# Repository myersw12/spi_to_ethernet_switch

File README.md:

# spi_to_ethernet_switch
Hardware and software for an Ethernet Switch with an MII to SPI adapter on it.

## Description

This project has 2 parts; a Kicad Project containing the schematic and layout for the board, and the software to interact 
with the board.  The idea was to create a compact ethernet switch suitable for use with low power microcontrollers and single 
board computers.  Micrel produces several ethernet switches in the same family with more ports and this design would make a good 
starting point for using those.

## Kicad Project

The main components of this project are the [Micrel KSZ8863MLL](https://www.microchip.com/wwwproducts/en/KSZ8863) 3 Port Ethernet Switch and the Wiznet W3150A+ Ethernet MAC to SPI Adapter.
The KSZ8863MLL provides 3 ethernet interfaces.  The first 2 include the PHYs and are connected to RJ45 connectors with included magnetics.
The other interface is connected via the MII interface to the [W3150A+](http://www.wiznet.io/product-item/w3150a/).  The SPI pins on W3150A+ are broken out on the board so that they
may be attached to a microcontroller or single board computer.  All of the examples in this project use a Raspberry Pi 2.

## Software

The software is located in the [code](/code) directory.  This was written for the Raspberry Pi 2 and it is easiest to compile it
on the raspberry pi.  Once it is there, run the makefile in the [src](/code/src) directory.  This creates three executables:
  * tx_example: transmits a raw ethernet frame once a second
  * recv_example: receives raw ethernet frames and prints them as they arrive
  * tap_example: uses the tap interface on the Raspberry Pi to send and receive raw ethernet frames over the SPI interface
  
The W3150A+ offers TCP/IP processing onboard.  Depending on the situation, it might be advantageous to make use of that functionality.
The existing SPI connection will support this.

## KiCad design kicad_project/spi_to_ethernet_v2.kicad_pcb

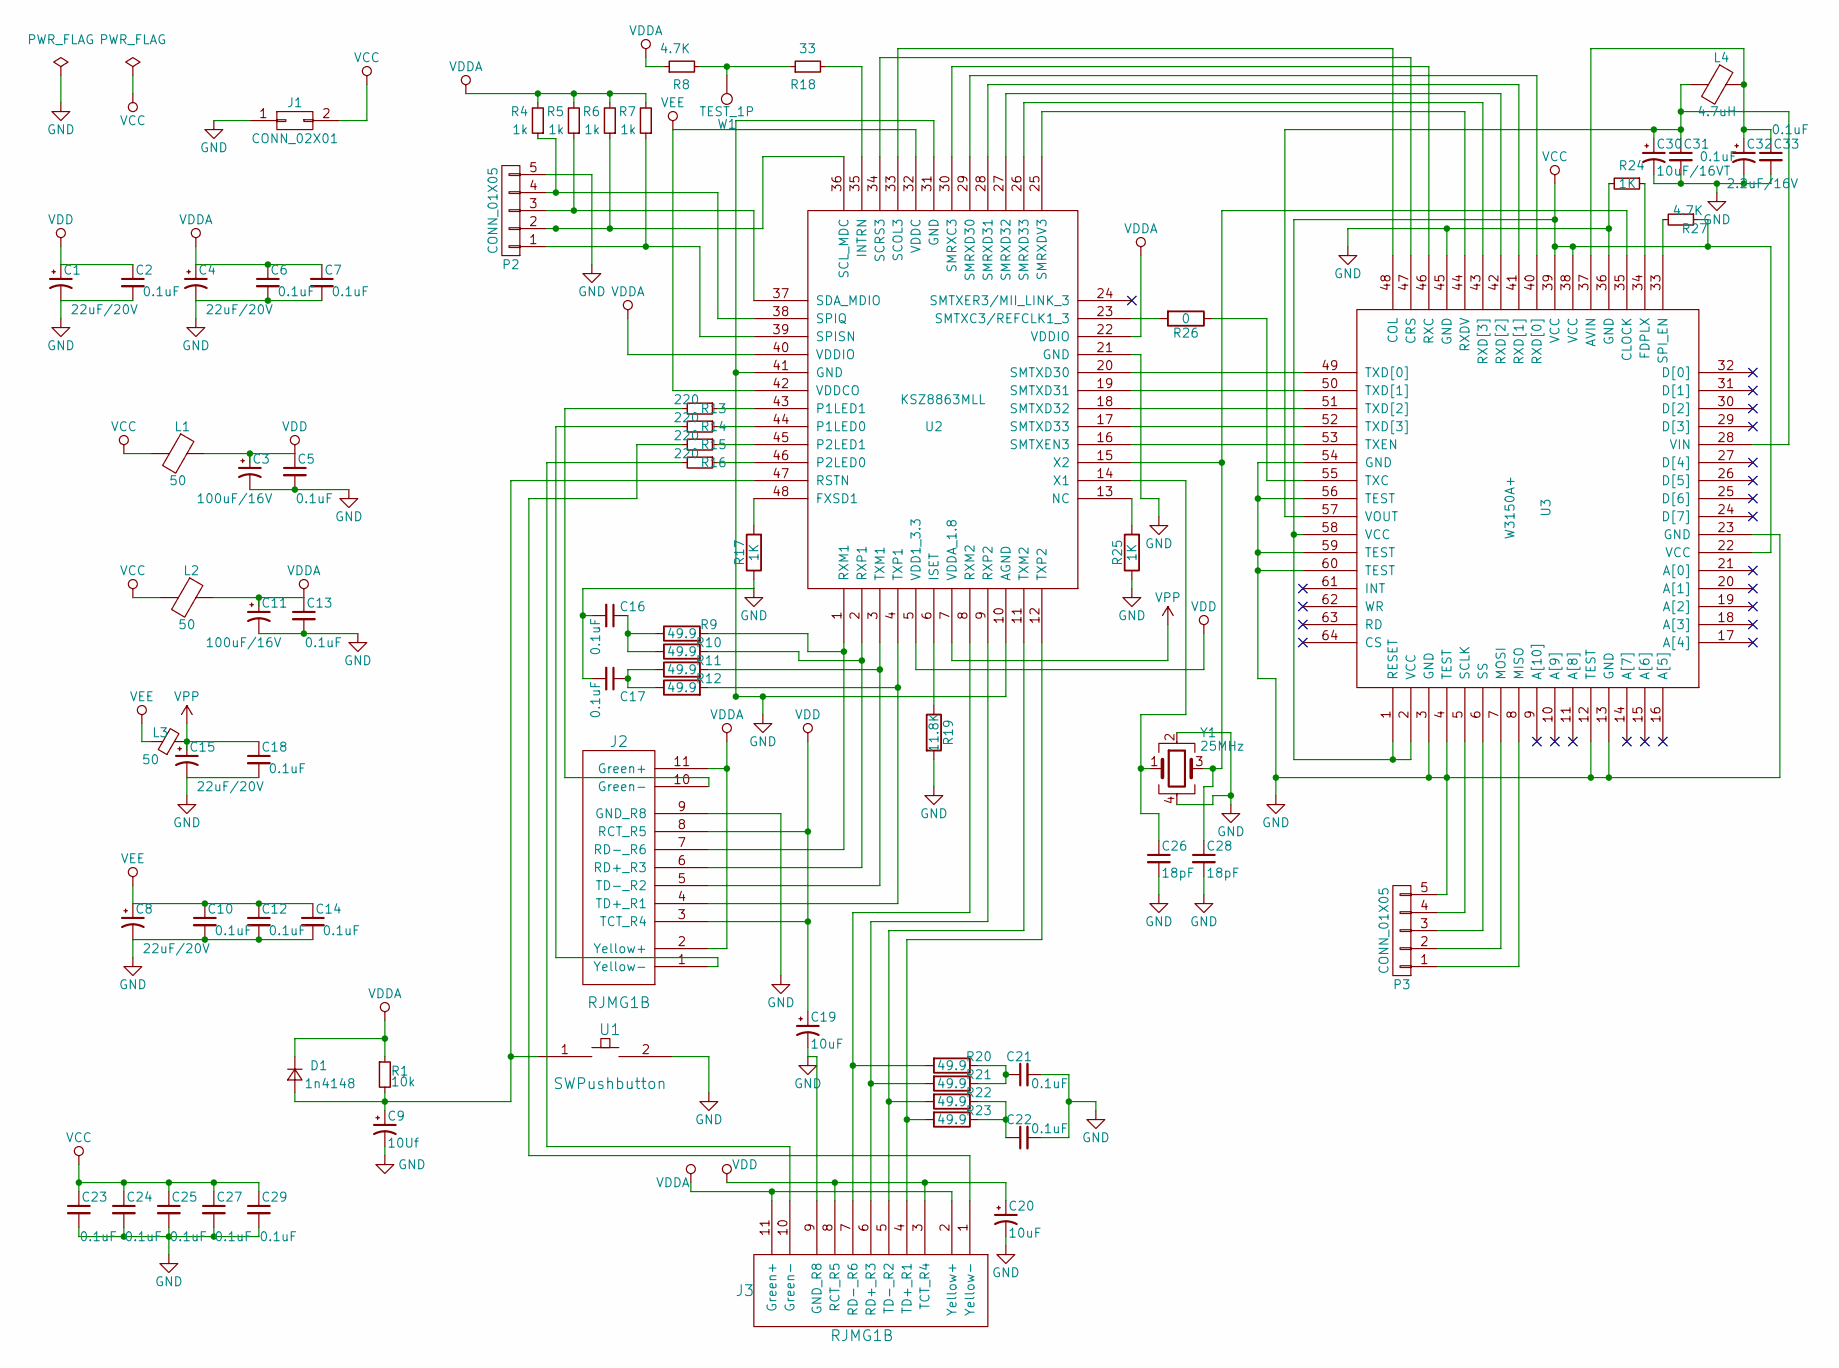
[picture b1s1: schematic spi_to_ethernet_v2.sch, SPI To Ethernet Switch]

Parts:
C1, C4, C8, C15: 22uF/20V; C_0805_HandSoldering
C2, C5, C6, C7, C10, C12, C13, C14, C16, C17, C18, C21, C22, C23, C24, C25, C27, C29, C31, C33: 0.1uF; C_0402
C3, C11: 100uF/16V; C_1210_HandSoldering
C9: 10Uf; C_0603_HandSoldering
C19, C20: 10uF; C_0603_HandSoldering
C26, C28: 18pF; C_0402
C30: 10uF/16VT; C_0603_HandSoldering
C32: 2.2uF/16V; C_0603_HandSoldering
D1: 1n4148; D_SOD-123
J1: CONN_02X01; Pin_Header_Straight_2x01_Pitch2.54mm
J2, J3: RJMG1B
L1, L2, L3: 50; C_1206_HandSoldering
L4: 4.7uH; C_1206_HandSoldering
P2, P3: CONN_01X05; Pin_Header_Straight_1x05_Pitch2.54mm
R1: 10k; R_0402
R4, R5, R6, R7: 1k; R_0402
R8, R27: 4.7K; R_0402
R9, R10, R11, R12, R20, R21, R22, R23: 49.9; R_0402
R13, R14, R15, R16: 220; R_0402
R17, R24, R25: 1K; R_0402
R18: 33; R_0402
R19: 11.8K; R_0402
R26: 0; R_0402
U1: SWPushbutton; SW_SPST_EVQQ2
U2: KSZ8863MLL; LQFP-48_7x7mm_Pitch0.5mm
U3: W3150A+; LQFP-64_10x10mm_Pitch0.5mm
W1: TEST_1P; Measurement_Point_Round-SMD-Pad_Big
Y1: 25MHz; Crystal_SMD_Abracon_ABM8G-4pin_3.2x2.5mm

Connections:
GND: C1.2, C2.2, C3.2, C4.2, C5.2, C6.2, C7.2, C8.2, C9.2, C10.2, C11.2, C12.2, C13.2, C14.2, C15.2, C16.2, C17.2, C18.2, C19.2, C20.2, C21.2, C22.2, C23.2, C24.2, C25.2, C26.2, C27.2, C28.2, C29.2, C30.2, C31.2, C32.2, C33.2, J1.1, J2.9 (GND_R8), J3.9 (GND_R8), P2.5, P3.5, R17.1, R19.2, R24.2, R25.1, U1.2, U2.10 (AGND), U2.21 (GND), U2.31 (GND), U2.41 (GND), U3.3 (GND), U3.4 (TEST), U3.12 (TEST), U3.13 (GND), U3.23 (GND), U3.36 (GND), U3.45 (GND), U3.54 (GND), U3.56 (TEST), U3.59 (TEST), U3.60 (TEST), Y1.2, Y1.4
unnamed: C9.1, D1.2 (A), R1.2, U1.1, U2.47 (RSTN)
unnamed: C16.1, R9.1, R10.1
unnamed: C17.1, R11.1, R12.1
unnamed: C21.1, R20.1, R21.1
unnamed: C22.1, R22.1, R23.1
unnamed: C26.1, U2.14 (X1), Y1.1
unnamed: C28.1, U2.15 (X2), U3.35 (CLOCK), Y1.3
unnamed: C30.1, C31.1, L4.2, U3.28 (VIN), U3.57 (VOUT)
unnamed: C32.1, C33.1, L4.1, U3.37 (AVIN)
unnamed: J2.1 (Yellow-), R14.2
unnamed: J2.4 (TD+_R1), R12.2, U2.4 (TXP1)
unnamed: J2.5 (TD-_R2), R11.2, U2.3 (TXM1)
unnamed: J2.6 (RD+_R3), R10.2, U2.2 (RXP1)
unnamed: J2.7 (RD-_R6), R9.2, U2.1 (RXM1)
unnamed: J2.10 (Green-), R13.2
unnamed: J3.1 (Yellow-), R15.2
unnamed: J3.4 (TD+_R1), R23.2, U2.12 (TXP2)
unnamed: J3.5 (TD-_R2), R22.2, U2.11 (TXM2)
unnamed: J3.6 (RD+_R3), R21.2, U2.9 (RXP2)
unnamed: J3.7 (RD-_R6), R20.2, U2.8 (RXM2)
unnamed: J3.10 (Green-), R16.2
unnamed: P2.1, R7.1, U2.39 (SPISN)
unnamed: P2.2, R6.1, U2.36 (SCL_MDC)
unnamed: P2.3, R5.1, U2.37 (SDA_MDIO)
unnamed: P2.4, R4.1, U2.38 (SPIQ)
unnamed: P3.1, U3.8 (MISO)
unnamed: P3.2, U3.7 (MOSI)
unnamed: P3.3, U3.6 (SS)
unnamed: P3.4, U3.5 (SCLK)
unnamed: R13.1, U2.43 (P1LED1)
unnamed: R14.1, U2.44 (P1LED0)
unnamed: R15.1, U2.45 (P2LED1)
unnamed: R16.1, U2.46 (P2LED0)
unnamed: R17.2, U2.48 (FXSD1)
unnamed: R8.2, R18.1, W1.1
unnamed: R18.2, U2.35 (INTRN)
unnamed: R19.1, U2.6 (ISET)
unnamed: R24.1, U3.34 (FDPLX)
unnamed: R25.2, U2.13 (NC)
unnamed: R26.1, U3.55 (TXC)
unnamed: R26.2, U2.23 (SMTXC3/REFCLK1_3)
unnamed: R27.2, U3.33 (SPI_EN)
unnamed: U2.16 (SMTXEN3), U3.53 (TXEN)
unnamed: U2.17 (SMTXD33), U3.52 (TXD[3])
unnamed: U2.18 (SMTXD32), U3.51 (TXD[2])
unnamed: U2.19 (SMTXD31), U3.50 (TXD[1])
unnamed: U2.20 (SMTXD30), U3.49 (TXD[0])
unnamed: U2.25 (SMRXDV3), U3.44 (RXDV)
unnamed: U2.26 (SMRXD33), U3.43 (RXD[3])
unnamed: U2.27 (SMRXD32), U3.42 (RXD[2])
unnamed: U2.28 (SMRXD31), U3.41 (RXD[1])
unnamed: U2.29 (SMRXD30), U3.40 (RXD[0])
unnamed: U2.30 (SMRXC3), U3.46 (RXC)
unnamed: U2.33 (SCOL3), U3.48 (COL)
unnamed: U2.34 (SCRS3), U3.47 (CRS)
VCC: C23.1, C24.1, C25.1, C27.1, C29.1, J1.2, L1.2, L2.2, R27.1, U3.1 (RESET), U3.2 (VCC), U3.22 (VCC), U3.38 (VCC), U3.39 (VCC), U3.58 (VCC)
VDD: C1.1, C2.1, C3.1, C5.1, C19.1, C20.1, J2.3 (TCT_R4), J2.8 (RCT_R5), J3.3 (TCT_R4), J3.8 (RCT_R5), L1.1, U2.5 (VDD1_3.3)
VDDA: C4.1, C6.1, C7.1, C11.1, C13.1, D1.1 (K), J2.2 (Yellow+), J2.11 (Green+), J3.2 (Yellow+), J3.11 (Green+), L2.1, R1.1, R4.2, R5.2, R6.2, R7.2, R8.1, U2.22 (VDDIO), U2.40 (VDDIO)
VEE: C8.1, C10.1, C12.1, C14.1, L3.1, U2.32 (VDDC), U2.42 (VDDCO)
VPP: C15.1, C18.1, L3.2, U2.7 (VDDA_1.8)

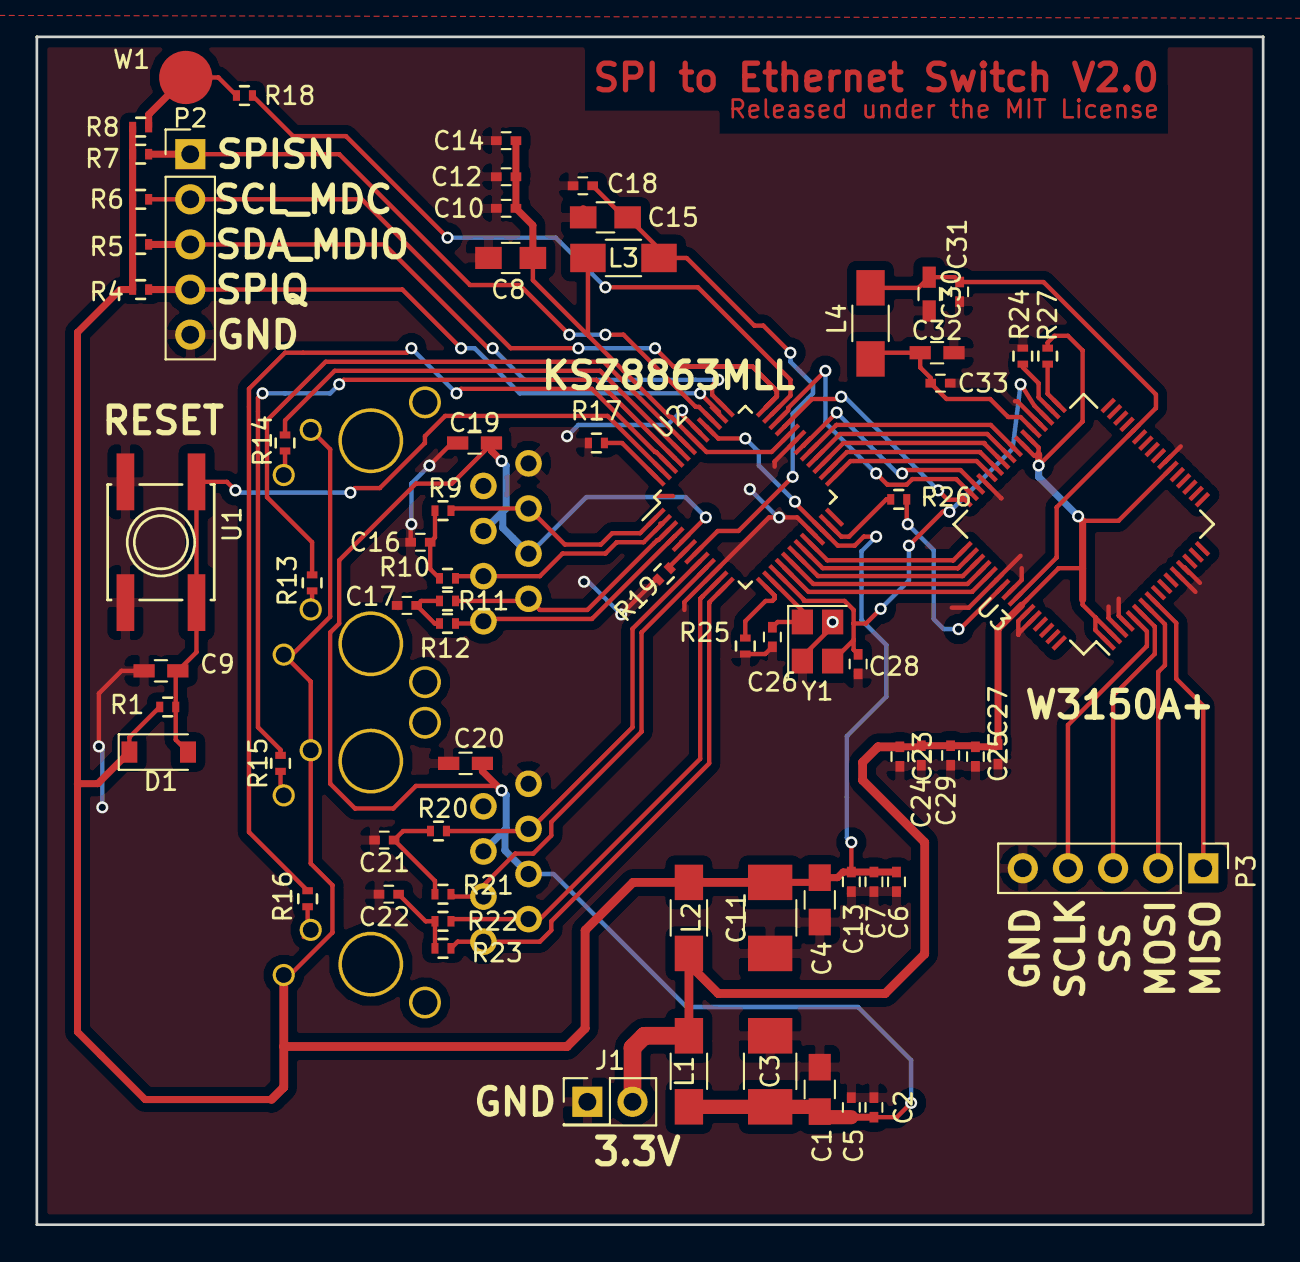
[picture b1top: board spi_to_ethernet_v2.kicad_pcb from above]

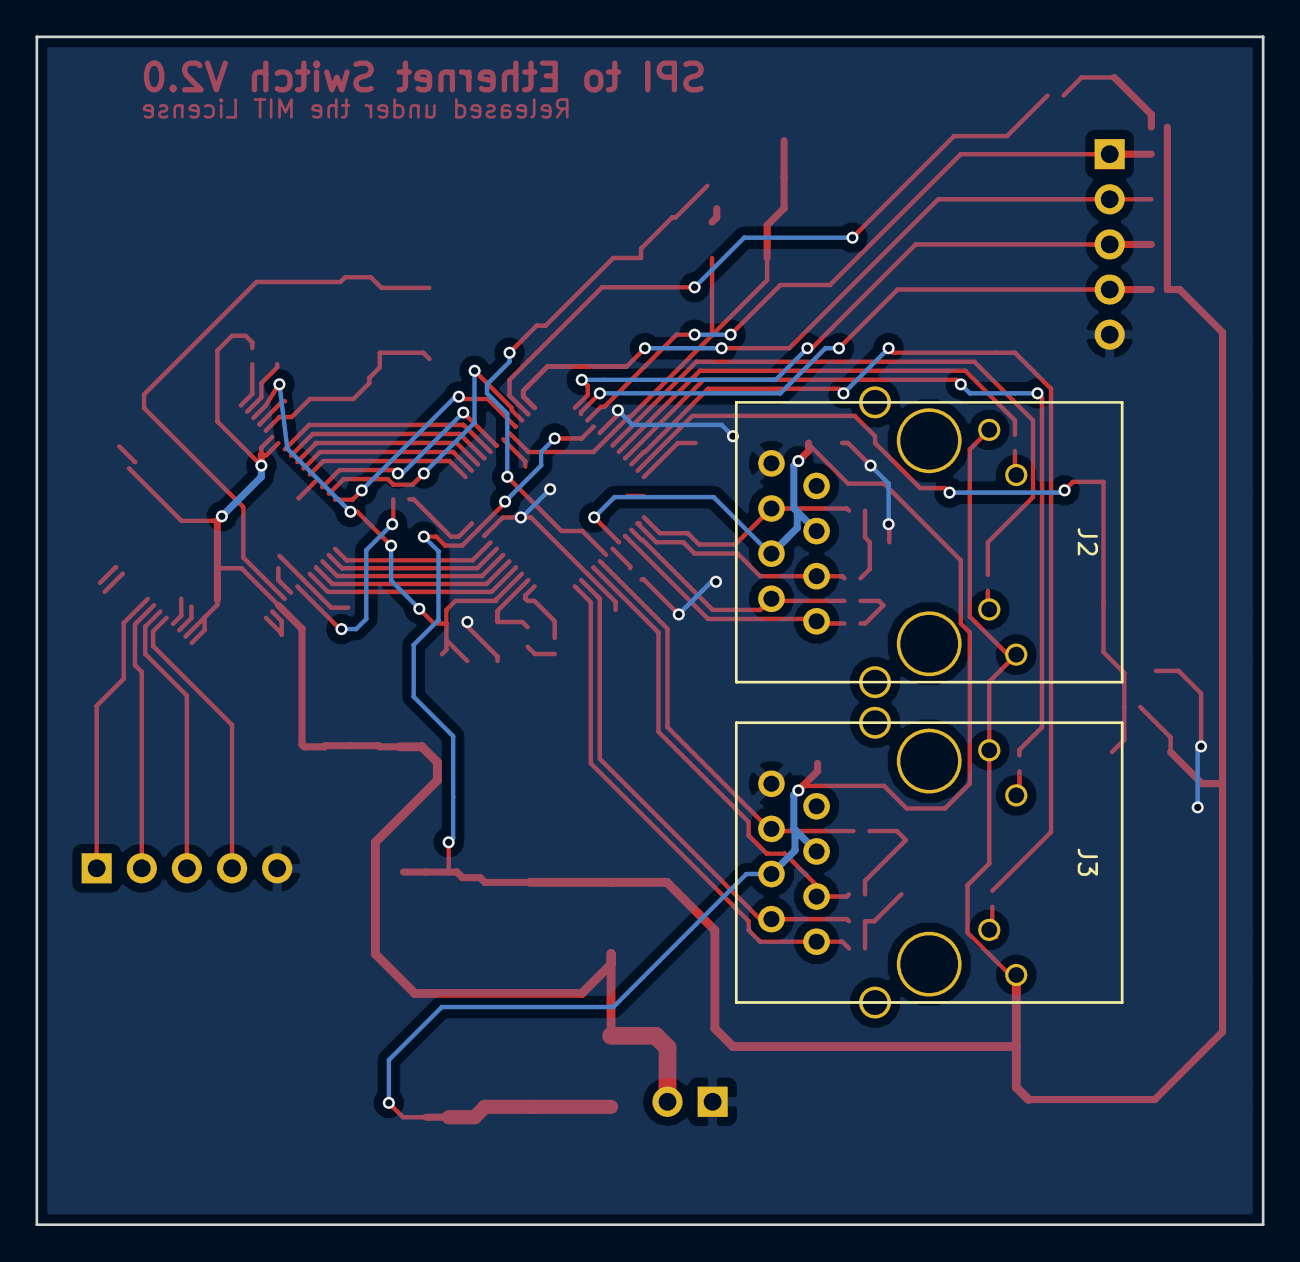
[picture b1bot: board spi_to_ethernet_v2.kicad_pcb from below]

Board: 2 copper layers, 69.0 x 66.9 mm, 73 parts (2 on the bottom side), 61 nets.

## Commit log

2018-04-15 adding everything
2018-04-15 adding readme for examples
2018-04-15 renamed to pdf

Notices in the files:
kicad_project/spi_to_ethernet_v2.kicad_pcb:
Released under the MIT License
